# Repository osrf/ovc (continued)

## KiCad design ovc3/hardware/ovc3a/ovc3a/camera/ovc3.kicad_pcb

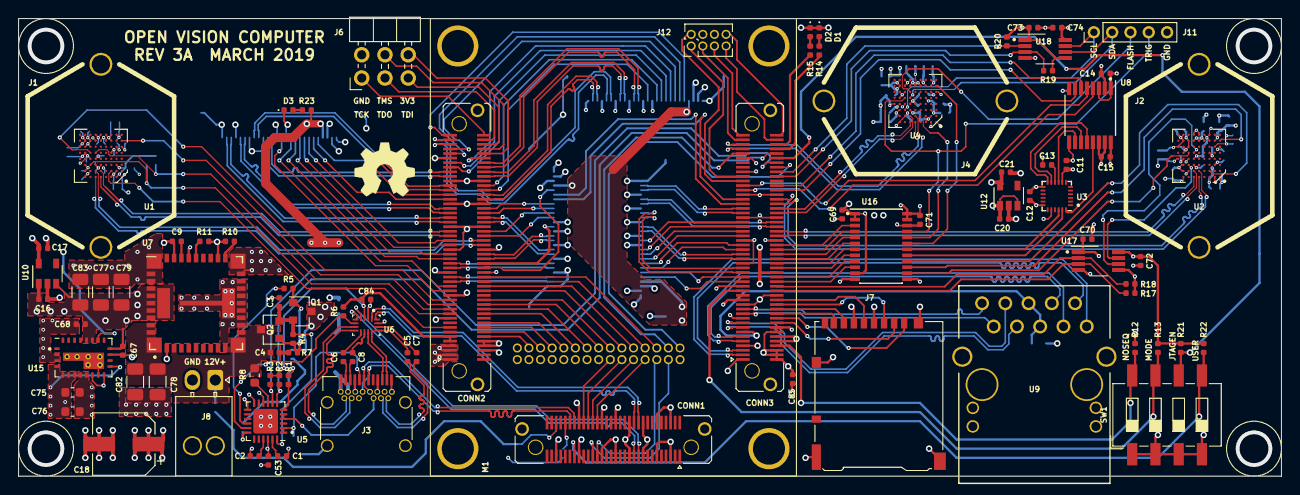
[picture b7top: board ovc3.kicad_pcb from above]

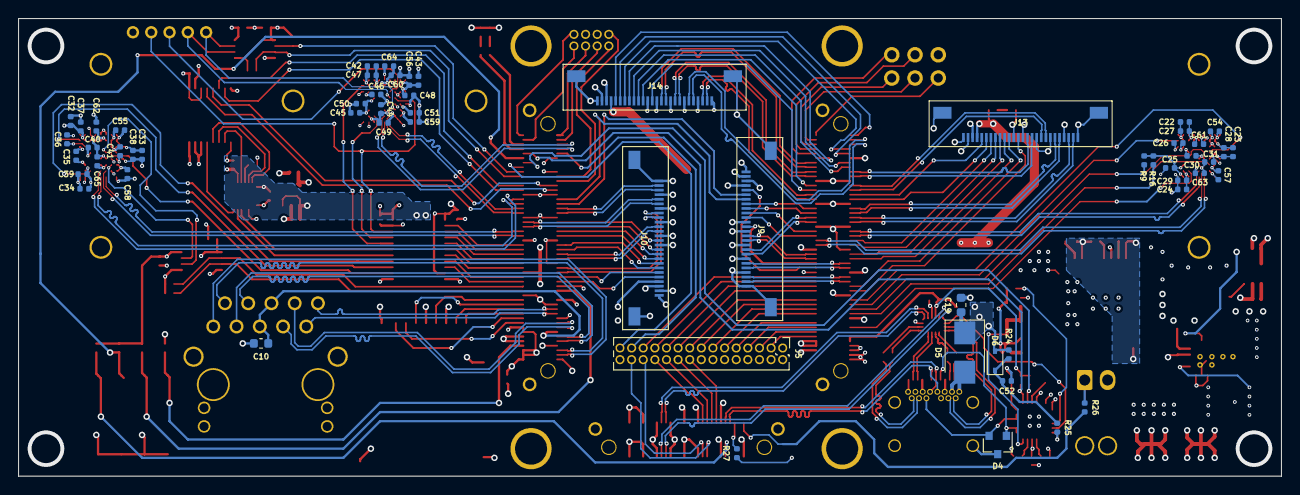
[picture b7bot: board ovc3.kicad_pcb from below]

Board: 6 copper layers, 138.0 x 50.0 mm, 149 parts (59 on the bottom side), 219 nets.

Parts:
C1, C2, C3, C16, C17, C20, C21, C52, C67: 1u; C_0402_1005Metric
C4, C5, C6, C7, C8, C11, C12, C13, C14, C15, C26, C27, C28, C29, C30, C31, C36, C37, C38, C39, C40, C41, C44, C47, C48, C49, C50, C51, C53, C54, C55, C56, C57, C58, C59, C60, C61, C62, C63, C64, C65, C69, C70, C71, C72, C73, C74, C84, C85: 100n; C_0402_1005Metric
C9: 3n3; C_0402_1005Metric
C10: 100n; C_0603_1608Metric
C18: 680u; CP_Elec_6.3x7.7
C19: 4u7; C_0603_1608Metric
C22, C23, C24, C25, C32, C33, C34, C35, C42, C43, C45, C46, C68: 10u; C_0402_1005Metric
C75, C76: 22u; C_0603_1608Metric
C77: 100u; C_1206_3216Metric
C78, C82: 22u; C_1206_3216Metric
C79, C83: 47u; C_1206_3216Metric
D1, D2, D3: LED; LED_0402_1005Metric
D4: ESDA25W; SOT-23
D5: SMBJ22A; D_SMB
D6: SDMK0340L-7-F; D_SOD-323
J1: LEFT_LENS; LENS_HOLDER_20MM_PT-LH010M
J2: RIGHT_LENS; LENS_HOLDER_20MM_PT-LH010M
J3: USB_C_Receptacle; USB_C_Receptacle_Wurth_632723300011
J4: MIDDLE_LENS; LENS_HOLDER_20MM_PT-LH010M
J5: LOW_SPEED_EXP; PinHeader_2x15_P1.27mm_Vertical
J6: JTAG; PinHeader_2x03_P2.54mm_Horizontal
J7: Micro_SD_Card_Det_Hirose_DM3AT; microSD_HC_Hirose_DM3AT-SF-PEJM5
J8: AUX_PWR; Molex_Nano-Fit_105313-xx02_1x02_P2.50mm_Horizontal
J9: BONUS1; MOLEX_505110_2691
J10: BONUS2; MOLEX_505110_2691
J11: CAM2_TIMING_DEBUG; PinHeader_1x05_P2.00mm_Vertical
J12: AUX; PinHeader_2x04_P1.27mm_Vertical
J13: BONUS3; MOLEX_505110_2691
J14: BONUS4; MOLEX_505110_2691
LOGO1: Logo_Open_Hardware_Small; OSHW-Symbol_6.7x6mm_SilkScreen
M1: TE0820
Q1, Q2: SI2369DS; SOT-23
R1, R4, R6: 100k; R_0402_1005Metric
R2, R3, R12, R13, R21, R22, R26: 10k; R_0402_1005Metric
R5: 22k; R_0402_1005Metric
R7: 100R; R_0402_1005Metric
R8: 1k; R_0603_1608Metric
R9, R16, R17, R18, R19, R20: 2k2; R_0402_1005Metric
R10: 90k9; R_0402_1005Metric
R11: 316R; R_0402_1005Metric
R14, R15, R23: 330R; R_0402_1005Metric
R24: 470; R_0402_1005Metric
R25, R27: 1k; R_0402_1005Metric
SW1: SW_DIP_x04; SW_DIP_SPSTx04_Slide_6.7x11.72mm_W8.61mm_P2.54mm_LowProfile
U1, U2, U4: AR0144CS; BGA-72_9x8_5.545x5.565mm
U3: ICM-20948; InvenSense_QFN-24_3x3mm_P0.4mm
U5: STUSB4500; QFN-24-1EP_4x4mm_P0.5mm_EP2.7x2.7mm
U6: HD3SS3202; TI_R_PUQFN_N16
U7: LMZ31707; TI_RVQ_42
U8: SN74AXC4T245; TSSOP-16_4.4x5mm_P0.65mm
U9: ARJ11C-MBSAS-A-BA-7MU2
U10, U12: LP5907MFX-2.8; SOT-23-5
U15: EN5322QI; Converter_DCDC_Intel_QFN-24_4x6mm_P0.65mm_ThermalVias
U16: SN74AXCH8T245; TSSOP-24_4.4x7.8mm_P0.65mm
U17, U18: TCA9803; VSSOP-8_3.0x3.0mm_P0.65mm

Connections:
3V3_VOUT: C84.2, M1.JB2.9, M1.JB2.11, R2.1, R3.1, R6.1, U6.3
+1V2: C14.1, C24.1, C26.1, C29.1, C31.1, C34.1, C36.1, C39.1, C41.1, C44.1, C46.1, C49.1, C51.1, C60.1, C61.1, C62.1, C63.1, C64.1, C65.1, C69.1, C70.1, C73.1, C75.1, C76.1, J5.12, J5.14, J9.25, J10.25, J12.4, J13.25, J14.25, M1.JB1.10, M1.JB1.12, M1.JB2.8, M1.JB2.10, R17.1, R18.1, R19.1, R20.1, U1.A3, U1.B2, U1.C5, U1.C6, U1.D8, U1.F2, U1.G4, U1.G5, U1.G6, U2.A3, U2.B2, U2.C5, U2.C6, U2.D8, U2.F2, U2.G4, U2.G5, U2.G6, U4.A3, U4.B2, U4.C5, U4.C6, U4.D8, U4.F2, U4.G4, U4.G5, U4.G6, U8.1, U8.3, U15.4, U15.5, U15.6, U15.7, U15.13, U16.1, U16.2, U16.11, U17.1, U17.5, U18.1, U18.5
+1V8: C11.1, C15.1, C25.1, C30.1, C35.1, C40.1, C45.1, C50.1, C57.1, C58.1, C59.1, C71.1, C72.1, C74.1, J5.1, J5.2, J9.24, J10.24, J13.24, J14.24, M1.JB1.40, M1.JB2.6, R9.1, R13.1, R16.1, R21.1, R22.1, U1.A2, U1.B8, U1.C2, U1.C8, U1.E3, U2.A2, U2.B8, U2.C2, U2.C8, U2.E3, U3.8, U4.A2, U4.B8, U4.C2, U4.C8, U4.E3, U8.16, U15.18, U16.23, U16.24, U17.8, U18.8
+3V3: C12.1, C16.1, C18.1, C20.1, C53.1, C67.1, C68.1, C77.1, C79.1, C83.1, C85.1, J5.6, J5.8, J7.4, J9.23, J10.23, J13.23, J14.23, M1.JB1.2, M1.JB1.4, M1.JB1.6, M1.JB1.14, M1.JB1.16, M1.JB1.27, M1.JB2.1, M1.JB2.3, M1.JB2.5, M1.JB2.7, R12.1, R23.1, R27.1, U3.13, U5.22, U7.27, U7.34, U7.35, U7.36, U7.37, U7.38, U7.41, U10.1, U10.3, U12.1, U12.3, U15.10, U15.12, U15.16, U15.19, U15.20
/imagers/CAM0_2V8: C17.1, C22.1, C23.1, C27.1, C28.1, C54.1, U1.F9, U1.G2, U1.G8, U1.H1, U1.H2, U1.H8, U1.H9, U10.5
/imagers/CAM1_2V8: C21.1, C32.1, C33.1, C37.1, C38.1, C42.1, C43.1, C47.1, C48.1, C55.1, C56.1, U2.F9, U2.G2, U2.G8, U2.H1, U2.H2, U2.H8, U2.H9, U4.F9, U4.G2, U4.G8, U4.H1, U4.H2, U4.H8, U4.H9, U12.5
/te0820/CAM1_EXTCLK_1V2: M1.JB1.42, U16.8
/te0820/CAM1_SCL_1V2: M1.JB1.34, R18.2, U17.2
/te0820/CAM1_SDA_1V2: M1.JB1.32, R17.2, U17.3
/te0820/CAM1_TRIG_1V2: M1.JB1.36, U16.10
/te0820/CAM1_nRESET_1V2: M1.JB1.38, U16.9
/te0820/CAM2_EXTCLK_1V2: M1.JB1.50, U16.4
/te0820/CAM2_SCL_1V2: M1.JB1.84, R20.2, U18.2
/te0820/CAM2_SDA_1V2: M1.JB1.82, R19.2, U18.3
/te0820/CAM2_TRIG_1V2: M1.JB1.52, U16.3
/te0820/CAM2_nRESET_1V2: M1.JB1.48, U16.5
/te0820/DIPSWITCH: M1.JB3.47, R22.2, SW1.5
/te0820/ICM_IMU_INT1_1V2: M1.JB1.77, U8.5
/te0820/ICM_SPI_CLK_1V2: M1.JB1.44, U16.7
/te0820/ICM_SPI_CS_1V2: M1.JB1.46, U16.6
/te0820/ICM_SPI_MISO_1V2: M1.JB1.75, U8.4
/te0820/ICM_SPI_MOSI_1V2: M1.JB1.76, U8.7
/te0820/ICM_SPI_SYNC_1V2: M1.JB1.78, U8.6
/te0820/JTAGEN: M1.JB1.90, R21.2, SW1.6
/te0820/MODE: M1.JB1.31, R13.2, SW1.7
/te0820/NOSEQ: M1.JB1.8, R12.2, SW1.8
/usb3/1V2: C2.1, U5.21
/usb3/2V7: C1.1, U5.23
/usb3/ABSIDE: R6.2, U5.17, U6.6
/usb3/CONN_CC1: D4.1, J3.A5, U5.1, U5.2
/usb3/CONN_CC2: D4.2, J3.B5, U5.4, U5.5
/usb3/CONN_RX1+: J3.B11, U6.8
/usb3/CONN_RX1-: J3.B10, U6.7
/usb3/CONN_RX2+: J3.A11, U6.12
/usb3/CONN_RX2-: J3.A10, U6.11
/usb3/CONN_TX1+: C6.2, J3.A2
/usb3/CONN_TX1-: C8.2, J3.A3
/usb3/CONN_TX2+: C5.2, J3.B2
/usb3/CONN_TX2-: C7.2, J3.B3
/usb3/CONN_VBUS: C19.1, D5.1, D6.2, J3.A4, J3.A9, J3.B4, J3.B9, Q1.3, R24.1
/usb3/DISCH: R8.2, U5.9
/usb3/GATES: Q1.1, Q2.1, R4.2, R5.1, R7.2
/usb3/PH: U7.10, U7.13, U7.14, U7.15, U7.16, U7.17, U7.18, U7.19, U7.42
/usb3/PWGND: C9.2, R10.2, R11.2, U7.2, U7.23, U7.29
/usb3/RESET: R1.1, U5.6
/usb3/T1+: C6.1, U6.9
/usb3/T1-: C8.1, U6.10
/usb3/T2+: C5.1, U6.13
/usb3/T2-: C7.1, U6.14
AUX0: J12.2, M1.JB1.79
AUX1: J12.1, M1.JB1.81
AUX2: J12.3, M1.JB1.97
AUX3: J12.5, M1.JB1.99
AUX4: J12.7, M1.JB1.98
AUX5: J12.8, M1.JB1.100
BONUS1_CLK0+: J9.2, M1.JB2.35
BONUS1_CLK0-: J9.3, M1.JB2.37
BONUS1_CLK1+: J9.8, M1.JB2.62
BONUS1_CLK1-: J9.9, M1.JB2.64
BONUS1_DAT0+: J9.5, M1.JB2.41
BONUS1_DAT0-: J9.6, M1.JB2.43
BONUS1_DAT1+: J9.11, M1.JB2.46
BONUS1_DAT1-: J9.12, M1.JB2.48
BONUS1_EXTCLK: J9.14, M1.JB2.44
BONUS1_FLASH: J9.20, M1.JB1.71
BONUS1_RESET: J9.21, M1.JB1.69
BONUS1_SCL0: J9.16, M1.JB2.56
BONUS1_SCL1: J9.18, M1.JB2.66
BONUS1_SDA0: J9.17, M1.JB2.58
BONUS1_SDA1: J9.19, M1.JB2.68
BONUS1_TRIGGER: J9.22, M1.JB2.42
BONUS2_CLK0+: J10.2, M1.JB1.67
BONUS2_CLK0-: J10.3, M1.JB1.65
BONUS2_CLK1+: J10.8, M1.JB1.39
BONUS2_CLK1-: J10.9, M1.JB1.41
BONUS2_DAT0+: J10.5, M1.JB1.62
BONUS2_DAT0-: J10.6, M1.JB1.60
BONUS2_DAT1+: J10.11, M1.JB1.47
BONUS2_DAT1-: J10.12, M1.JB1.45
BONUS2_EXTCLK: J10.14, M1.JB1.61
BONUS2_FLASH: J10.20, M1.JB1.49
BONUS2_RESET: J10.21, M1.JB1.37
BONUS2_SCL0: J10.16, M1.JB1.59
BONUS2_SCL1: J10.18, M1.JB1.55
BONUS2_SDA0: J10.17, M1.JB1.57
BONUS2_SDA1: J10.19, M1.JB1.51
BONUS2_TRIGGER: J10.22, M1.JB1.35
BONUS3_CLK0+: J13.2, M1.JB2.61
BONUS3_CLK0-: J13.3, M1.JB2.63
BONUS3_CLK1+: J13.8, M1.JB2.77
BONUS3_CLK1-: J13.9, M1.JB2.75
BONUS3_DAT0+: J13.5, M1.JB2.65
BONUS3_DAT0-: J13.6, M1.JB2.67
BONUS3_DAT1+: J13.11, M1.JB2.81
BONUS3_DAT1-: J13.12, M1.JB2.83
BONUS3_EXTCLK: J13.14, M1.JB2.31
BONUS3_FLASH: J13.20, M1.JB2.53
BONUS3_RESET: J13.21, M1.JB2.71
BONUS3_SCL0: J13.16, M1.JB2.33
BONUS3_SCL1: J13.18, M1.JB2.47
BONUS3_SDA0: J13.17, M1.JB2.45
BONUS3_SDA1: J13.19, M1.JB2.51
BONUS3_TRIGGER: J13.22, M1.JB2.73
BONUS4_CLK0+: J14.2, M1.JB2.72
BONUS4_CLK0-: J14.3, M1.JB2.74
BONUS4_CLK1+: J14.8, M1.JB2.82
BONUS4_CLK1-: J14.9, M1.JB2.84
BONUS4_DAT0+: J14.5, M1.JB2.95
BONUS4_DAT0-: J14.6, M1.JB2.97
BONUS4_DAT1+: J14.11, M1.JB2.86
BONUS4_DAT1-: J14.12, M1.JB2.88
BONUS4_EXTCLK: J14.14, M1.JB2.76
BONUS4_FLASH: J14.20, M1.JB2.93
BONUS4_RESET: J14.21, M1.JB2.91
BONUS4_SCL0: J14.16, M1.JB2.78
BONUS4_SCL1: J14.18, M1.JB2.87
BONUS4_SDA0: J14.17, M1.JB2.85
BONUS4_SDA1: J14.19, M1.JB2.90
BONUS4_TRIGGER: J14.22, M1.JB2.99
CAM0_CLK+: M1.JB2.55, U1.A5
CAM0_CLK-: M1.JB2.57, U1.B5
CAM0_D0+: M1.JB2.52, U1.A6
CAM0_D0-: M1.JB2.54, U1.B6
CAM0_EXTCLK_1V8: M1.JB2.15, U1.B3
CAM0_SCL_1V8: M1.JB2.21, R16.2, U1.C7
CAM0_SDA_1V8: M1.JB2.23, R9.2, U1.E6
CAM0_TRIG_1V8: M1.JB2.27, U1.E7
CAM0_nRESET_1V8: M1.JB2.25, U1.G1
CAM1_CLK+: M1.JB1.70, U2.A5
CAM1_CLK-: M1.JB1.72, U2.B5
CAM1_D0+: M1.JB1.58, U2.A6
CAM1_D0-: M1.JB1.56, U2.B6
CAM1_EXTCLK_1V8: U2.B3, U16.16
CAM1_SCL_1V8: U2.C7, U17.7
CAM1_SDA_1V8: U2.E6, U17.6
CAM1_TRIG_1V8: U2.E7, U16.14
CAM1_nRESET_1V8: U2.G1, U16.15
CAM2_CLK+: M1.JB1.95, U4.A5
CAM2_CLK-: M1.JB1.93, U4.B5
CAM2_D0+: M1.JB1.68, U4.A6
CAM2_D0-: M1.JB1.66, U4.B6
CAM2_EXTCLK_1V8: U4.B3, U16.20
CAM2_FLASH_1V8: J11.3, U4.F6
CAM2_SCL_1V8: J11.1, U4.C7, U18.7
CAM2_SDA_1V8: J11.2, U4.E6, U18.6
CAM2_TRIG_1V8: J11.4, U4.E7, U16.21
CAM2_nRESET_1V8: U4.G1, U16.19
ETH_VCC: C10.1, M1.JB1.13, U9.5, U9.6
GND: C1.2, C2.2, C3.2, C10.2, C11.2, C12.2, C13.2, C14.2, C15.2, C16.2, C17.2, C18.2, C19.2, C20.2, C21.2, C22.2, C23.2, C24.2, C25.2, C26.2, C27.2, C28.2, C29.2, C30.2, C31.2, C32.2, C33.2, C34.2, C35.2, C36.2, C37.2, C38.2, C39.2, C40.2, C41.2, C42.2, C43.2, C44.2, C45.2, C46.2, C47.2, C48.2, C49.2, C50.2, C51.2, C52.2, C53.2, C54.2, C55.2, C56.2, C57.2, C58.2, C59.2, C60.2, C61.2, C62.2, C63.2, C64.2, C65.2, C67.2, C68.2, C69.2, C70.2, C71.2, C72.2, C73.2, C74.2, C75.2, C76.2, C77.2, C78.2, C79.2, C82.2, C83.2, C84.1, C85.2, D1.1, D2.1, D3.1, D4.3, D5.2, J1.1, J2.1, J3.A1, J3.A12, J3.B1, J3.B12, J3.S1, J4.1, J5.4, J5.10, J5.16, J5.30, J6.2, J7.6, J7.11, J8.2, J9.1, J9.4, J9.7, J9.10, J9.13, J9.15, J9.26, J9.27, J10.1, J10.4, J10.7, J10.10, J10.13, J10.15, J10.26, J10.27, J11.5, J12.6, J13.1, J13.4, J13.7, J13.10, J13.13, J13.15, J13.26, J13.27, J14.1, J14.4, J14.7, J14.10, J14.13, J14.15, J14.26, J14.27, M1.JB1.1, M1.JB1.7, M1.JB1.19, M1.JB1.25, M1.JB1.30, M1.JB1.33, M1.JB1.43, M1.JB1.53, M1.JB1.54, M1.JB1.63, M1.JB1.64, M1.JB1.73, M1.JB1.74, M1.JB1.83, M1.JB1.89, M1.JB2.19, M1.JB2.29, M1.JB2.39, M1.JB2.40, M1.JB2.49, M1.JB2.50, M1.JB2.59, M1.JB2.60, M1.JB2.69, M1.JB2.70, M1.JB2.79, M1.JB2.80, M1.JB2.89, M1.JB3.5, M1.JB3.6, M1.JB3.11, M1.JB3.12, M1.JB3.17, M1.JB3.18, M1.JB3.23, M1.JB3.24, M1.JB3.29, M1.JB3.30, M1.JB3.35, M1.JB3.36, M1.JB3.45, M1.JB3.46, M1.JB3.55, R1.2, SW1.1, SW1.2, SW1.3, SW1.4, U1.A1, U1.A8, U1.B7, U1.D5, U1.D6, U1.D7, U1.D9, U1.E8, U1.F1, U1.F7, U1.F8, U1.G3, U1.G7, U1.H3, U1.H4, U1.H5, U1.H6, U1.H7, U2.A1, U2.A8, U2.B7, U2.D5, U2.D6, U2.D7, U2.D9, U2.E8, U2.F1, U2.F7, U2.F8, U2.G3, U2.G7, U2.H3, U2.H4, U2.H5, U2.H6, U2.H7, U3.18, U3.20, U4.A1, U4.A8, U4.B7, U4.D5, U4.D6, U4.D7, U4.D9, U4.E8, U4.F1, U4.F7, U4.F8, U4.G3, U4.G7, U4.H3, U4.H4, U4.H5, U4.H6, U4.H7, U5.10, U5.12, U5.13, U5.25, U6.2, U6.15, U7.20, U7.21, U7.31, U7.32, U7.33, U8.2, U8.8, U8.9, U8.14, U8.15, U9.11, U9.14, U9.MNT, U9.SHLD, U10.2, U12.2, U15.2, U15.3, U15.8, U15.9, U15.11, U15.15, U15.25, U16.12, U16.13, U16.22, U17.4, U18.4
GPIO0: J5.3, M1.JB2.12
GPIO1: J5.5, M1.JB2.14
GPIO2: J5.7, M1.JB2.16
GPIO3: J5.9, M1.JB2.18
GPIO4: J5.11, M1.JB2.22
GPIO5: J5.13, M1.JB2.24
GPIO6: J5.15, M1.JB2.26
GPIO7: J5.17, M1.JB2.28
GPIO8: J5.19, M1.JB2.32
GPIO9: J5.21, M1.JB2.34
GPIO10: J5.23, M1.JB2.36
GPIO11: J5.25, M1.JB2.38
GPIO12: J5.18, M1.JB3.44
GPIO13: J5.20, M1.JB3.42
GPIO14: J5.22, M1.JB3.40
GPIO15: J5.24, M1.JB3.38
GPIO16: J5.26, M1.JB3.37
GPIO17: J5.28, M1.JB3.39
ICM_IMU_INT1_1V8: U3.12, U8.12
ICM_IMU_SYNC_1V8: U3.11, U8.11
ICM_SPI_CLK_1V8: U3.23, U16.17
ICM_SPI_CS_1V8: U3.22, U16.18
ICM_SPI_MISO_1V8: U3.24, U8.13
ICM_SPI_MOSI_1V8: U3.9, U8.10
JTAG_TCK: J6.1, M1.JB2.100
JTAG_TDI: J6.5, M1.JB2.96
JTAG_TDO: J6.3, M1.JB2.98
JTAG_TMS: J6.4, M1.JB2.94
LED0: M1.JB1.94, R14.2
LED1: M1.JB1.96, R15.2
unnamed: C3.1, Q1.2, Q2.2, R4.1, U5.24
unnamed: C4.2, R7.1
unnamed: C9.1, U7.28
unnamed: C13.1, U3.10
unnamed: C52.1, D6.1, R24.2, R25.1
unnamed: D1.2, R14.1
unnamed: D2.2, R15.1
unnamed: D3.2, R23.2
unnamed: M1.JB3.52, R27.2
unnamed: M1.JB3.56, R26.2
unnamed: R5.2, U5.16
unnamed: R10.1, U7.22
unnamed: R11.1, U7.26
unnamed: R25.2, U5.18
PHY_MDI0_N: M1.JB1.5, U9.2
PHY_MDI0_P: M1.JB1.3, U9.1
PHY_MDI1_N: M1.JB1.11, U9.4
PHY_MDI1_P: M1.JB1.9, U9.3
PHY_MDI2_N: M1.JB1.17, U9.8
PHY_MDI2_P: M1.JB1.15, U9.7
PHY_MDI3_N: M1.JB1.23, U9.10
PHY_MDI3_P: M1.JB1.21, U9.9
ROOT_RX: J5.27, M1.JB1.91
ROOT_TX: J5.29, M1.JB1.86
SD_CLK: J7.5, M1.JB1.28
SD_CMD: J7.3, M1.JB1.26
SD_DAT0: J7.7, M1.JB1.24
SD_DAT1: J7.8, M1.JB1.22
SD_DAT2: J7.1, M1.JB1.20
SD_DAT3: J7.2, M1.JB1.18
USB2_D+: J3.A6, J3.B6, M1.JB3.48
USB2_D-: J3.A7, J3.B7, M1.JB3.50
USB3_RX+: M1.JB3.19, U6.4
USB3_RX-: M1.JB3.21, U6.5
USB3_TX+: M1.JB3.22, U6.16
USB3_TX-: M1.JB3.20, U6.1
USB_SCL: M1.JB1.92, R2.2, U5.7
USB_SDA: M1.JB1.88, R3.2, U5.8
VBUS: C4.1, C78.1, C82.1, J8.1, Q2.3, R8.1, R26.1, U7.1, U7.3, U7.11, U7.12, U7.39, U7.40
VCC_JTAG: J6.6, M1.JB2.92
